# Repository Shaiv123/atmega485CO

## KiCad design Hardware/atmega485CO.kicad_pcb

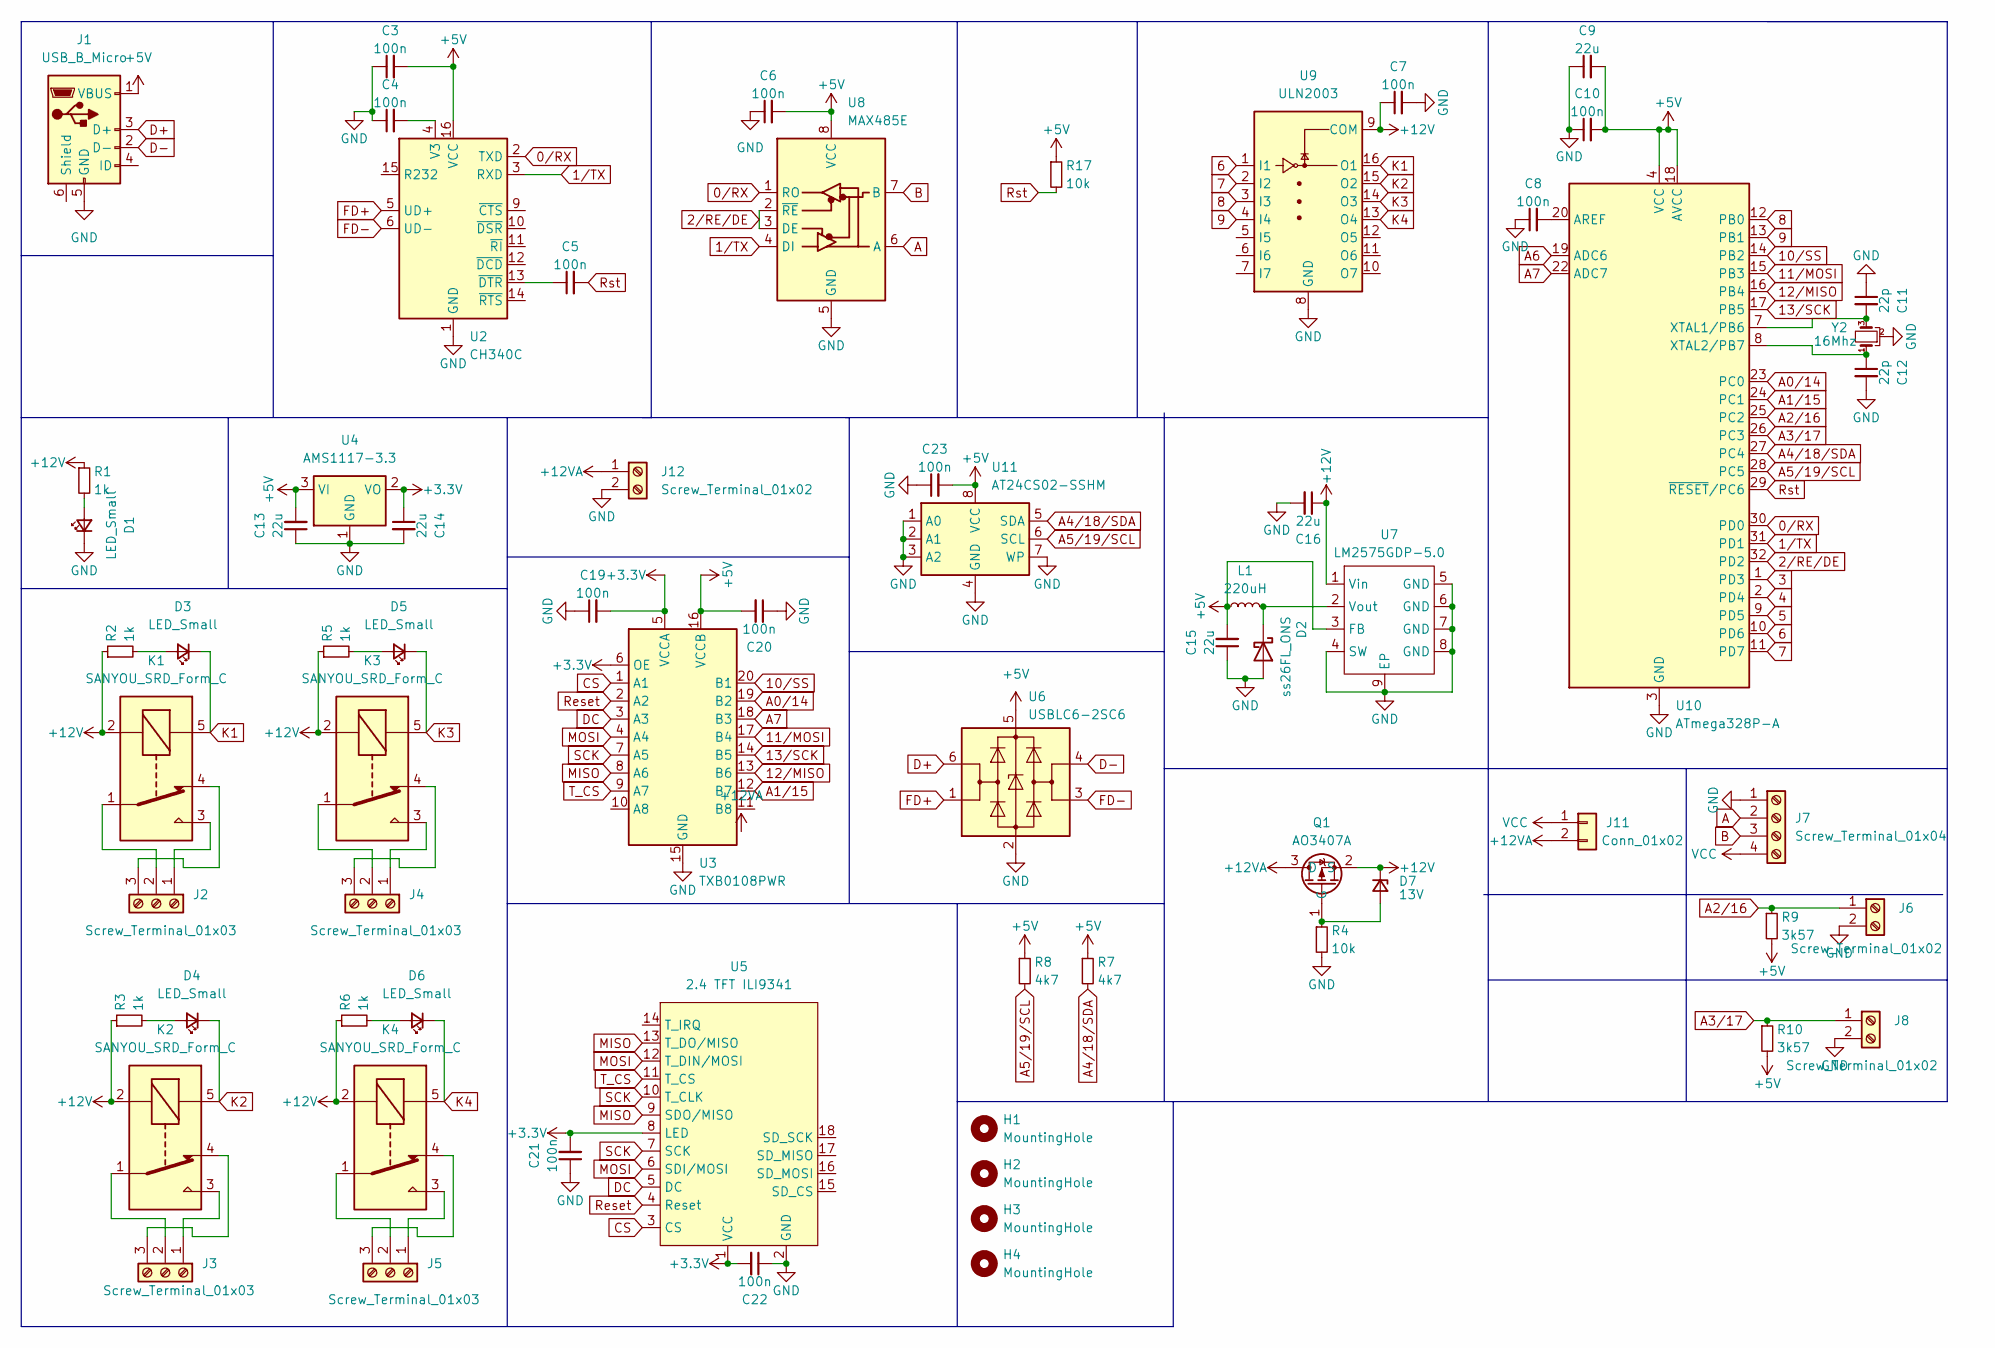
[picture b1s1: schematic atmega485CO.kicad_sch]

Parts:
C3, C4, C5, C6, C7, C8, C10, C19, C20, C21, C22, C23: 100n; C_0805_2012Metric_Pad1.18x1.45mm_HandSolder
C9, C13, C14, C15, C16: 22u; C_0805_2012Metric_Pad1.18x1.45mm_HandSolder
C11, C12: 22p; C_0603_1608Metric_Pad1.08x0.95mm_HandSolder
D1, D3, D4, D5, D6: LED_Small; LED_0805_2012Metric_Pad1.15x1.40mm_HandSolder
D2: ss26FL_ONS; D_SOD-123F
D7: 13V; D_SOD-323_HandSoldering
H1, H2, H3, H4: MountingHole; MountingHole_3.2mm_M3_Pad
J1: USB_B_Micro; USB_Micro-B_Amphenol_10118194_Horizontal
J2, J3, J4, J5: Screw_Terminal_01x03; TerminalBlock_Phoenix_MKDS-1,5-3_1x03_P5.00mm_Horizontal
J6, J8, J12: Screw_Terminal_01x02; PhoenixContact_MC_1,5_2-G-3.5_1x02_P3.50mm_Horizontal
J7: Screw_Terminal_01x04; PhoenixContact_MC_1,5_4-G-3.81_1x04_P3.81mm_Horizontal
J11: Conn_01x02; PinHeader_1x02_P2.54mm_Vertical
K1, K2, K3, K4: SANYOU_SRD_Form_C; Relay_SPDT_SANYOU_SRD_Series_Form_C
L1: 220uH; L_12x12mm_H6mm
Q1: AO3407A; SOT-23-3
R1, R2, R3, R5, R6: 1k; R_0805_2012Metric_Pad1.20x1.40mm_HandSolder
R4, R17: 10k; R_0805_2012Metric_Pad1.20x1.40mm_HandSolder
R7, R8: 4k7; R_0805_2012Metric_Pad1.20x1.40mm_HandSolder
R9, R10: 3k57; R_0805_2012Metric_Pad1.20x1.40mm_HandSolder
U2: CH340C; SOIC-16_3.9x9.9mm_P1.27mm
U3: TXB0108PWR; TSSOP-20_4.4x6.5mm_P0.65mm
U4: AMS1117-3.3; SOT-223-3_TabPin2
U5: 2.4 TFT ILI9341; 2.4 tft ILI9341
U6: USBLC6-2SC6; SOT-23-6
U7: LM2575GDP-5.0; SOP-8-1EP_4.57x4.57mm_P1.27mm_EP4.57x4.45mm_ThermalVias
U8: MAX485E; SO-8_3.9x4.9mm_P1.27mm
U9: ULN2003; SO-16_3.9x9.9mm_P1.27mm
U10: ATmega328P-A; TQFP-32_7x7mm_P0.8mm
U11: AT24CS02-SSHM; SOIC-8_3.9x4.9mm_P1.27mm
Y2: 16Mhz; Resonator_SMD_Murata_CSTxExxV-3Pin_3.0x1.1mm_HandSoldering

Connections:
0/RX: U2.2 (TXD), U8.1 (RO), U10.30 (PD0)
1/TX: U2.3 (RXD), U8.4 (DI), U10.31 (PD1)
2/RE/DE: U8.2 (~RE), U8.3 (DE), U10.32 (PD2)
3: U10.1 (PD3)
4: U10.2 (PD4)
5: U10.9 (PD5)
6: U9.1 (I1), U10.10 (PD6)
7: U9.2 (I2), U10.11 (PD7)
8: U9.3 (I3), U10.12 (PB0)
9: U9.4 (I4), U10.13 (PB1)
10/SS: U3.20 (B1), U10.14 (PB2)
11/MOSI: U3.17 (B4), U10.15 (PB3)
12/MISO: U3.13 (B6), U10.16 (PB4)
13/SCK: U3.14 (B5), U10.17 (PB5)
+3.3V: C14.1, C19.2, C21.2, C22.2, U3.5 (VCCA), U3.6 (OE), U4.2 (VO), U5.1 (VCC), U5.8 (LED)
+5V: C3.2, C6.2, C9.2, C10.2, C13.2, C15.2, C20.2, C23.2, J1.1 (VBUS), L1.1, R7.1, R8.1, R9.2, R10.2, R17.1, U2.16 (VCC), U3.16 (VCCB), U4.3 (VI), U6.5 (VBUS), U7.3 (FB), U8.8 (VCC), U10.4 (VCC), U10.6 (VCC), U10.18 (AVCC), U11.8 (VCC)
+12V: C7.1, C16.1, D7.1 (K), K1.2, K2.2, K3.2, K4.2, Q1.2 (S), R1.1, R2.1, R3.1, R5.1, R6.1, U7.1 (Vin), U9.9 (COM)
+12VA: J11.2, J12.1, Q1.3 (D)
A: J7.2, U8.6 (A)
A0/14: U3.19 (B2), U10.23 (PC0)
A1/15: U3.12 (B7), U10.24 (PC1)
A2/16: J6.1, R9.1, U10.25 (PC2)
A3/17: J8.1, R10.1, U10.26 (PC3)
A4/18/SDA: R7.2, U10.27 (PC4), U11.5 (SDA)
A5/19/SCL: R8.2, U10.28 (PC5), U11.6 (SCL)
A6: U10.19 (ADC6)
A7: U3.18 (B3), U10.22 (ADC7)
B: J7.3, U8.7 (B)
CS: U3.1 (A1), U5.3 (CS)
D+: J1.3 (D+), U6.6 (I/O1)
D-: J1.2 (D-), U6.4 (I/O2)
DC: U3.3 (A3), U5.5 (DC)
FD+: U2.5 (UD+), U6.1 (I/O1)
FD-: U2.6 (UD-), U6.3 (I/O2)
GND: C3.1, C4.1, C6.1, C7.2, C8.1, C9.1, C10.1, C11.1, C12.2, C13.1, C14.2, C15.1, C16.2, C19.1, C20.1, C21.1, C22.1, C23.1, D1.1 (K), D2.2 (A), J1.5 (GND), J6.2, J7.1, J8.2, J12.2, R4.2, U2.1 (GND), U3.15 (GND), U4.1 (GND), U5.2 (GND), U6.2 (GND), U7.4 (SW), U7.5 (GND), U7.6 (GND), U7.7 (GND), U7.8 (GND), U7.9 (EP), U8.5 (GND), U9.8 (GND), U10.3 (GND), U10.5 (GND), U10.21 (GND), U11.1 (A0), U11.2 (A1), U11.3 (A2), U11.4 (GND), U11.7 (WP), Y2.2
K1: D3.1 (K), K1.5, U9.16 (O1)
K2: D4.1 (K), K2.5, U9.15 (O2)
K3: D5.1 (K), K3.5, U9.14 (O3)
K4: D6.1 (K), K4.5, U9.13 (O4)
MISO: U3.8 (A6), U5.9 (SDO/MISO), U5.13 (T_DO/MISO)
MOSI: U3.4 (A4), U5.6 (SDI/MOSI), U5.12 (T_DIN/MOSI)
unnamed: D1.2 (A), R1.2
unnamed: D2.1 (K), L1.2, U7.2 (Vout)
unnamed: D3.2 (A), R2.2
unnamed: D4.2 (A), R3.2
unnamed: D5.2 (A), R5.2
unnamed: D6.2 (A), R6.2
unnamed: D7.2 (A), Q1.1 (G), R4.1
unnamed: J2.1, K1.3
unnamed: J2.2, K1.1
unnamed: J2.3, K1.4
unnamed: J3.1, K2.3
unnamed: J3.2, K2.1
unnamed: J3.3, K2.4
unnamed: J4.1, K3.3
unnamed: J4.2, K3.1
unnamed: J4.3, K3.4
unnamed: J5.1, K4.3
unnamed: J5.2, K4.1
unnamed: J5.3, K4.4
unnamed: C4.2, U2.4 (V3)
unnamed: C5.1, U2.13 (~DTR)
unnamed: C8.2, U10.20 (AREF)
unnamed: C11.2, U10.7 (XTAL1/PB6), Y2.3
unnamed: C12.1, U10.8 (XTAL2/PB7), Y2.1
Reset: U3.2 (A2), U5.4 (Reset)
Rst: C5.2, R17.2, U10.29 (~RESET/PC6)
SCK: U3.7 (A5), U5.7 (SCK), U5.10 (T_CLK)
T_CS: U3.9 (A7), U5.11 (T_CS)
VCC: J7.4, J11.1

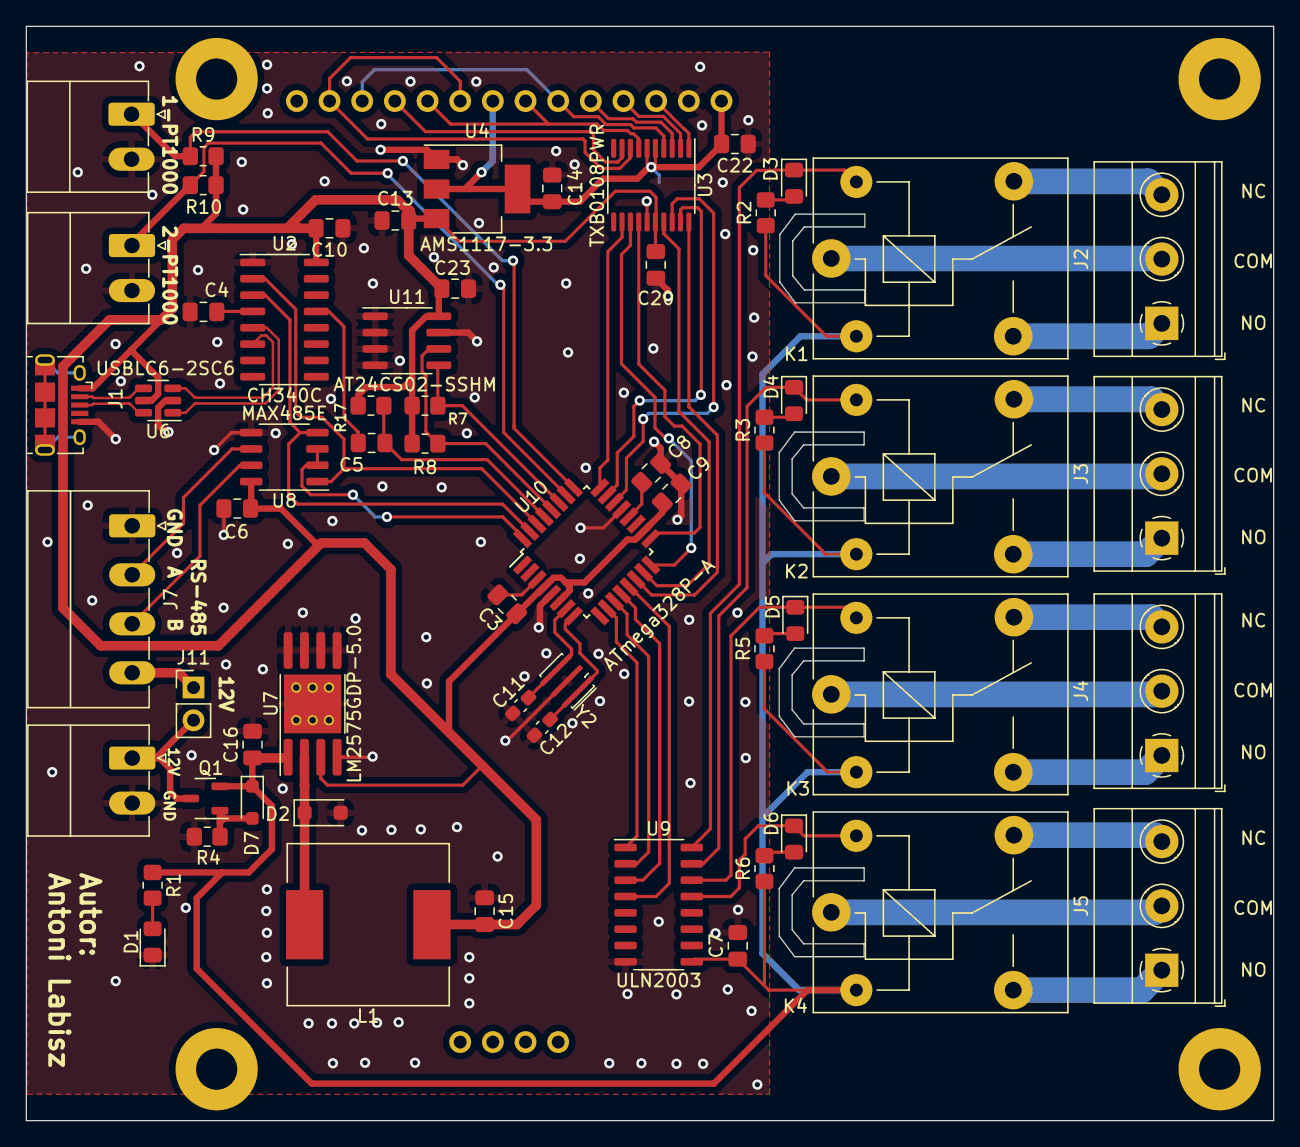
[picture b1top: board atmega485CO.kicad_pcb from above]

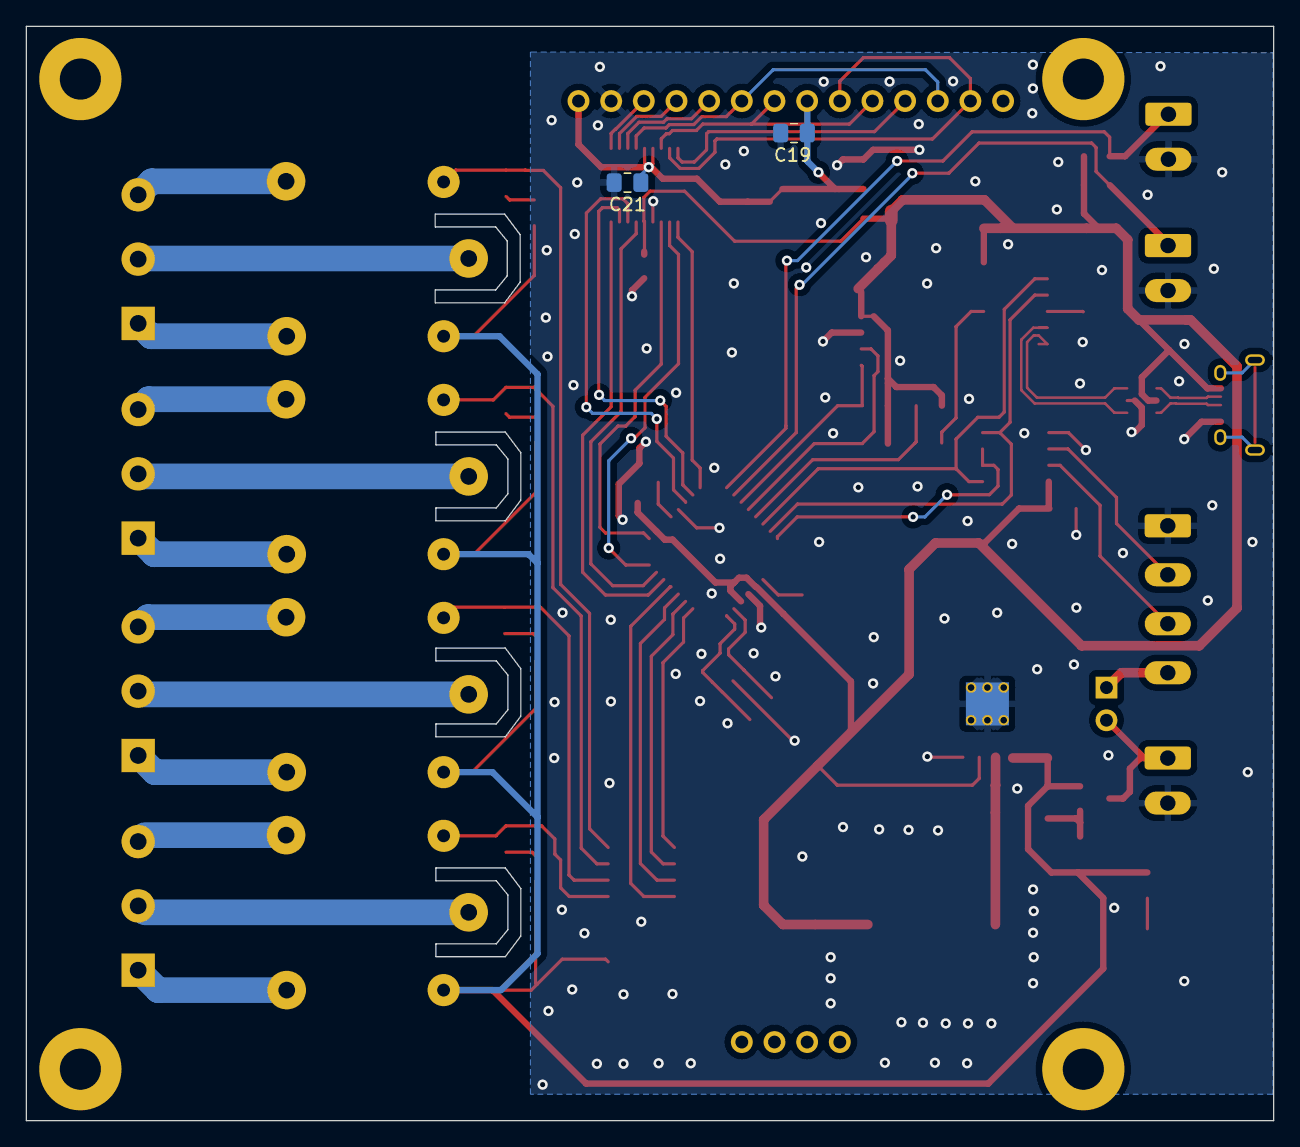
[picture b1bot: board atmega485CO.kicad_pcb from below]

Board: 2 copper layers, 97.0 x 85.1 mm, 68 parts (2 on the bottom side), 66 nets.

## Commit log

2024-10-13 Initial
